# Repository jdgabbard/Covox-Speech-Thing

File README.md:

# Covox-Speech-Thing
Covox Speech Thing Clone

This repository is a clone of the Covox Speech Thing designed to fit inside of a DB25 Plastic Hood.  There are two different versions provided.

The first is a mono version.  The second is designed for 'Stereo' jacks.  However, they both emit mono sound.

Design files provided are for Eagle 7.  But should work with other versions of eagle as well.  I have also included gerbers for manufacturing.

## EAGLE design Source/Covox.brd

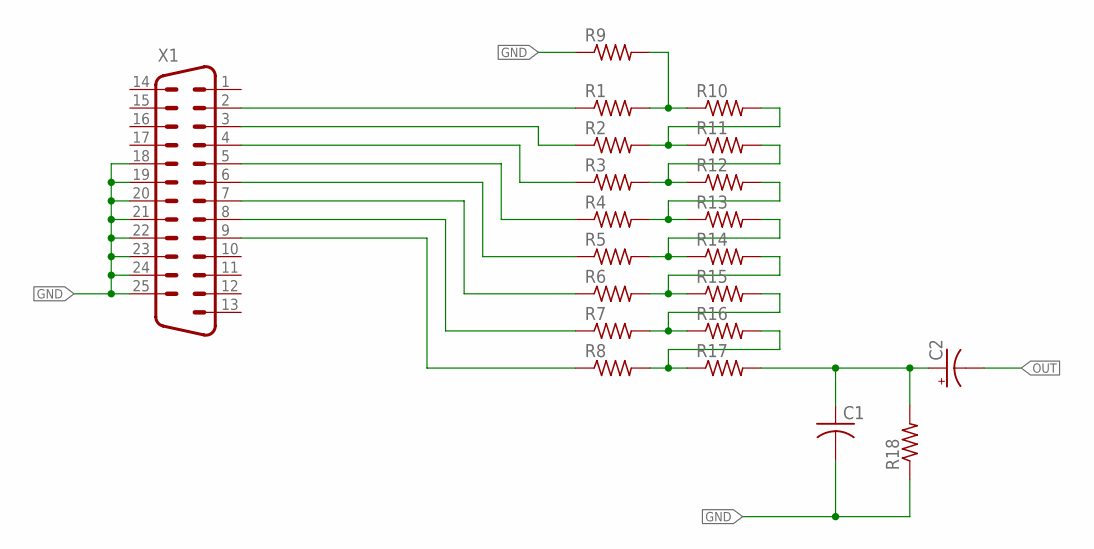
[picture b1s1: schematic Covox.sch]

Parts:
C1: C-USC0805K; C0805K
C2: CPOL-US153CLV-0405; 153CLV-0405
R1, R2, R3, R4, R5, R6, R7, R8, R9, R10, R11, R12, R13, R14, R15, R16, R17, R18: R-US_M0805; M0805
X1: DB25D; M25D

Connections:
GND: C1.2, R9.1, R18.1, X1.18, X1.19, X1.20, X1.21, X1.22, X1.23, X1.24, X1.25
unnamed: R1.1, X1.2
unnamed: R2.1, X1.3
unnamed: R3.1, X1.4
unnamed: R4.1, X1.5
unnamed: R5.1, X1.6
unnamed: R6.1, X1.7
unnamed: R7.1, X1.8
unnamed: R8.1, X1.9
unnamed: R1.2, R9.2, R10.1
unnamed: R2.2, R10.2, R11.1
unnamed: R3.2, R11.2, R12.1
unnamed: R4.2, R12.2, R13.1
unnamed: R5.2, R13.2, R14.1
unnamed: R6.2, R14.2, R15.1
unnamed: R7.2, R15.2, R16.1
unnamed: R8.2, R16.2, R17.1
unnamed: C1.1, C2.+, R17.2, R18.2
OUT: C2.-

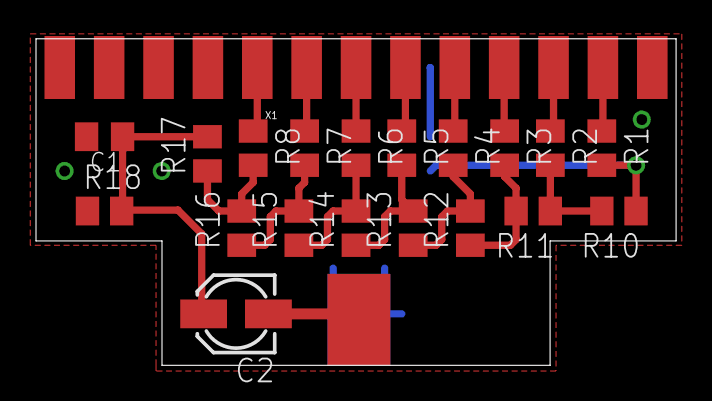
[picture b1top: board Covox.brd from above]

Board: 2 copper layers, 35.6 x 18.1 mm, 21 parts (1 on the bottom side), 18 nets.

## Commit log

2022-02-26 Initial Upload`
    Initial upload of the design files and gerbers.
2022-02-26 Photo Upload

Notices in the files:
parts and their libraries:
SparkFun-Connectors: Licensing: Creative Commons ShareAlike 4.0 International - https://creativecommons.org/licenses/by-sa/4.0
